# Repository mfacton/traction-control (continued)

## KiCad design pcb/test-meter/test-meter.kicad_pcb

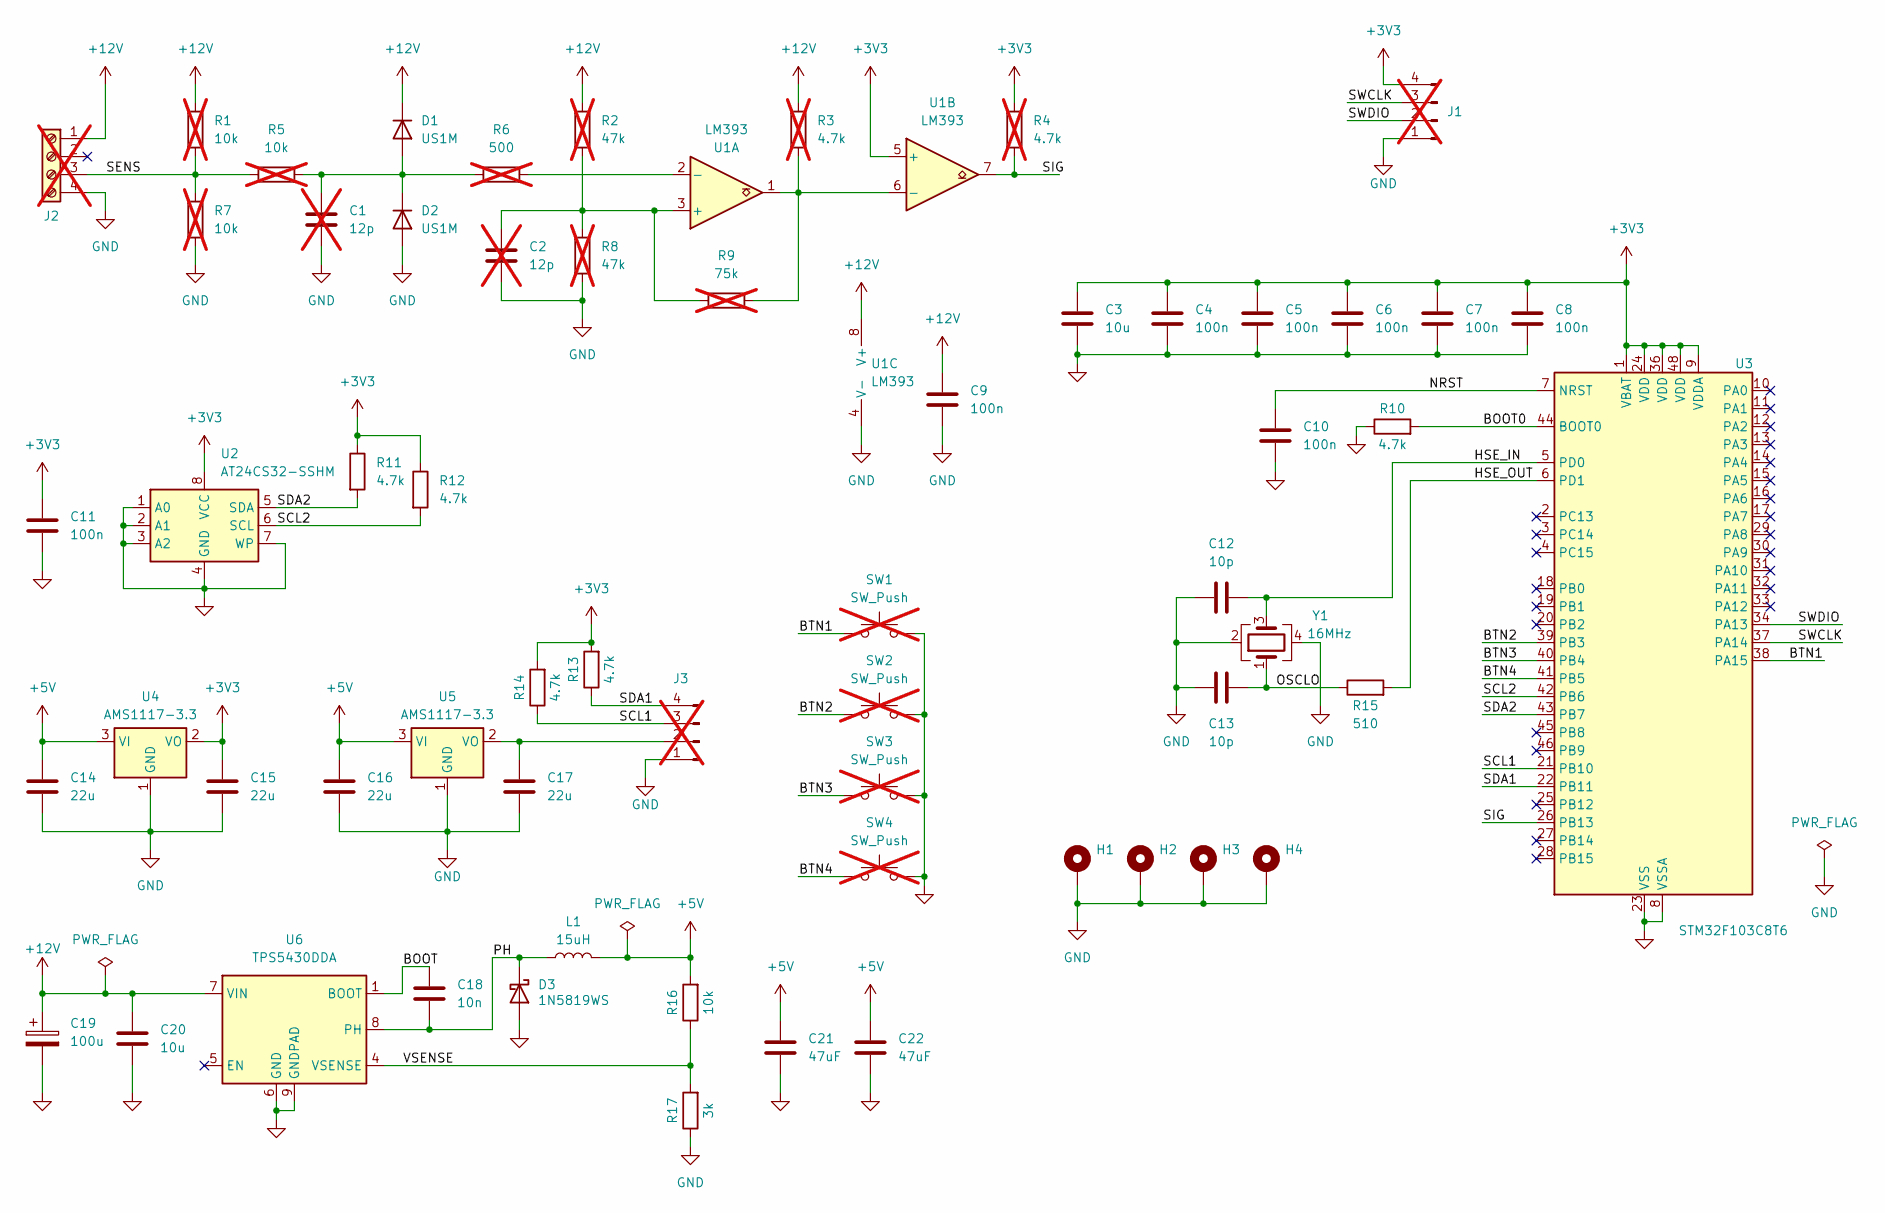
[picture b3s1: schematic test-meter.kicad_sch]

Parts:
C1, C2: 12p; C_Disc_D5.0mm_W2.5mm_P5.00mm; not fitted
C3: 10u; C_0603_1608Metric
C4, C5, C6, C7, C8, C9, C10, C11: 100n; C_0402_1005Metric
C12, C13: 10p; C_0402_1005Metric
C14, C15, C16, C17: 22u; C_0805_2012Metric
C18: 10n; C_0603_1608Metric
C19: 100u; C_Elec_8x6.2; LCSC C178539
C20: 10u; C_0805_2012Metric
C21, C22: 47uF; C_1206_3216Metric; LCSC C96123
D1, D2: US1M; D_SMA
D3: 1N5819WS; D_SOD-323
H1, H2, H3, H4: MountingHole_Pad; MountingHole_3.2mm_M3_DIN965_Pad
J1, J3: Conn_01x04_Pin; PinHeader_1x04_P2.54mm_Vertical; not fitted
J2: Screw_Terminal_01x04; TerminalBlock_bornier-4_P5.08mm; not fitted
L1: 15uH; L_Changjiang_FNR3010S; LCSC C222856
R1, R5, R7: 10k; R_Axial_DIN0207_L6.3mm_D2.5mm_P10.16mm_Horizontal; LCSC C17902; not fitted
R2, R8: 47k; R_Axial_DIN0207_L6.3mm_D2.5mm_P10.16mm_Horizontal; LCSC C25792; not fitted
R3, R4: 4.7k; R_Axial_DIN0207_L6.3mm_D2.5mm_P10.16mm_Horizontal; not fitted
R6: 500; R_Axial_DIN0207_L6.3mm_D2.5mm_P10.16mm_Horizontal; LCSC C17902; not fitted
R9: 75k; R_Axial_DIN0207_L6.3mm_D2.5mm_P10.16mm_Horizontal; LCSC C25798; not fitted
R10, R11, R12: 4.7k; R_0402_1005Metric; LCSC C25900
R13, R14: 4.7k; R_0402_1005Metric
R15: 510; R_0402_1005Metric; LCSC C25123
R16: 10k; R_0402_1005Metric; LCSC C25744
R17: 3k; R_0603_1608Metric_Pad0.98x0.95mm_HandSolder
SW1, SW2, SW3, SW4: SW_Push; SW_PUSH_6mm; not fitted
U1: LM393; SOIC-8_3.9x4.9mm_P1.27mm; LCSC C7955
U2: AT24CS32-SSHM; SOIC-8_3.9x4.9mm_P1.27mm; LCSC C6482
U3: STM32F103C8T6; LQFP-48_7x7mm_P0.5mm; LCSC C8734
U4, U5: AMS1117-3.3; SOT-223-3_TabPin2
U6: TPS5430DDA; TI_SO-PowerPAD-8_ThermalVias; LCSC C9864
Y1: 16MHz; Crystal_SMD_3225-4Pin_3.2x2.5mm

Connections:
+3V3: C3.1, C4.1, C5.1, C6.1, C7.1, C8.1, C11.1, C15.1, J1.4, R4.1, R11.1, R12.1, R13.2, R14.2, U1.5 (+), U2.8 (VCC), U3.1 (VBAT), U3.9 (VDDA), U3.24 (VDD), U3.36 (VDD), U3.48 (VDD), U4.2 (VO)
+5V: C14.1, C16.1, C21.1, C22.1, L1.2, R16.2, U4.3 (VI), U5.3 (VI)
+12V: C9.1, C19.1, C20.1, D1.1 (K), J2.1, R1.1, R2.1, R3.1, U1.8 (V+), U6.7 (VIN)
/BOOT: C18.1, U6.1 (BOOT)
/BOOT0: R10.2, U3.44 (BOOT0)
/BTN1: SW1.1, U3.38 (PA15)
/BTN2: SW2.1, U3.39 (PB3)
/BTN3: SW3.1, U3.40 (PB4)
/BTN4: SW4.1, U3.41 (PB5)
/HSE_IN: C12.2, U3.5 (PD0), Y1.3
/HSE_OUT: R15.2, U3.6 (PD1)
/NRST: C10.1, U3.7 (NRST)
/OSCLO: C13.2, R15.1, Y1.1
/PH: C18.2, D3.1 (K), L1.1, U6.8 (PH)
/SCL1: J3.3, R14.1, U3.21 (PB10)
/SCL2: R12.2, U2.6 (SCL), U3.42 (PB6)
/SDA1: J3.4, R13.1, U3.22 (PB11)
/SDA2: R11.2, U2.5 (SDA), U3.43 (PB7)
/SENS: J2.3, R1.2, R5.1, R7.1
/SIG: R4.2, U1.7, U3.26 (PB13)
/SWCLK: J1.3, U3.37 (PA14)
/SWDIO: J1.2, U3.34 (PA13)
/VSENSE: R16.1, R17.2, U6.4 (VSENSE)
GND: C1.2, C2.2, C3.2, C4.2, C5.2, C6.2, C7.2, C8.2, C9.2, C10.2, C11.2, C12.1, C13.1, C14.2, C15.2, C16.2, C17.2, C19.2, C20.2, C21.2, C22.2, D2.2 (A), D3.2 (A), H1.1, H2.1, H3.1, H4.1, J1.1, J2.4, J3.1, R7.2, R8.2, R10.1, R17.1, SW1.2, SW2.2, SW3.2, SW4.2, U1.4 (V-), U2.1 (A0), U2.2 (A1), U2.3 (A2), U2.4 (GND), U2.7 (WP), U3.8 (VSSA), U3.23 (VSS), U3.35 (VSS), U3.47 (VSS), U4.1 (GND), U5.1 (GND), U6.6 (GND), U6.9 (GNDPAD), Y1.2, Y1.4
unnamed: C1.1, D1.2 (A), D2.1 (K), R5.2, R6.1
unnamed: C17.1, J3.2, U5.2 (VO)
unnamed: C2.1, R2.2, R8.1, R9.1, U1.3 (+)
unnamed: R6.2, U1.2 (-)
unnamed: R3.2, R9.2, U1.1, U1.6 (-)

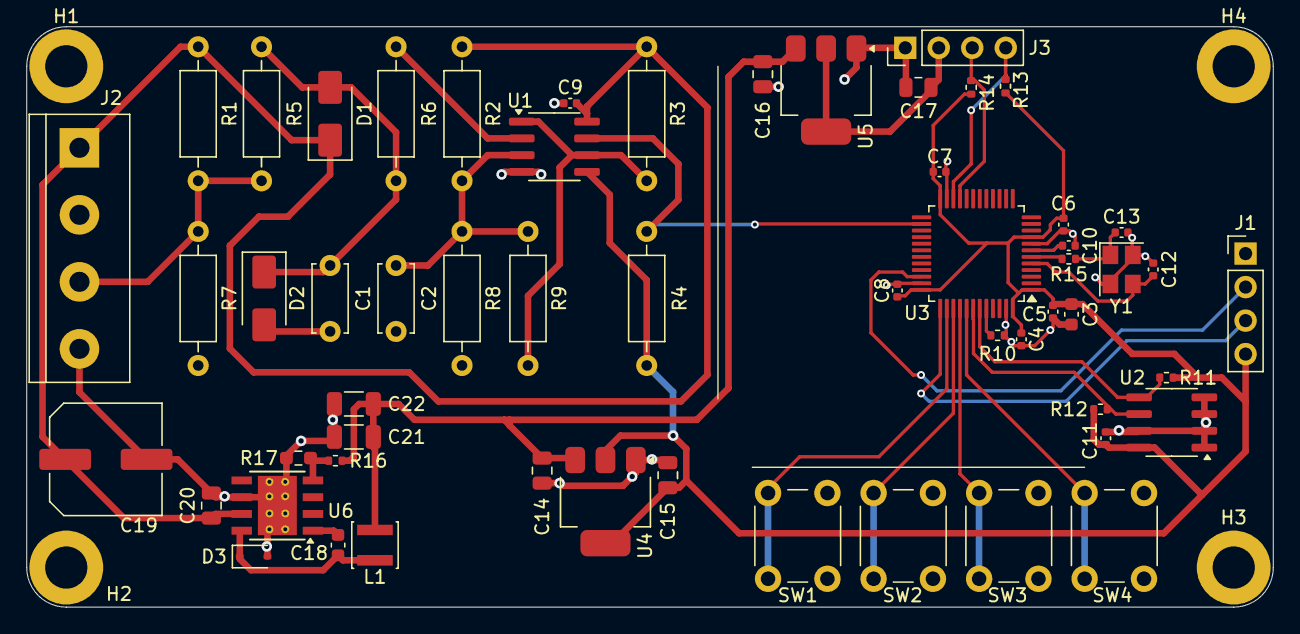
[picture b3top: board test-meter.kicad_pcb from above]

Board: 2 copper layers, 94.5 x 44.0 mm, 61 parts (0 on the bottom side), 29 nets.

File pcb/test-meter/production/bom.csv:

Designator,Footprint,Quantity,Value,LCSC Part #
"C10, C11, C4, C5, C6, C7, C8, C9",0402,8,100n,
"C12, C13",0402,2,10p,
"C14, C15, C16, C17",0805,4,22u,
C18,0603,1,10n,
C19,C_Elec_8x6.2,1,100u,C178539
C20,0805,1,10u,
"C21, C22",1206,2,47uF,C96123
C3,0603,1,10u,
"D1, D2",D_SMA,2,US1M,
D3,D_SOD-323,1,1N5819WS,
L1,L_Changjiang_FNR3010S,1,15uH,C222856
"R10, R11, R12",0402,3,4.7k,C25900
"R13, R14",0402,2,4.7k,
R15,0402,1,510,C25123
R16,0402,1,10k,C25744
R17,0603,1,3k,
U1,SOIC-8_3.9x4.9mm_P1.27mm,1,LM393,C7955
U2,SOIC-8_3.9x4.9mm_P1.27mm,1,AT24CS32-SSHM,C6482
U3,LQFP-48_7x7mm_P0.5mm,1,STM32F103C8T6,C8734
"U4, U5",SOT-223-3_TabPin2,2,AMS1117-3.3,
U6,TI_SO-PowerPAD-8_ThermalVias,1,TPS5430DDA,C9864
Y1,Crystal_SMD_3225-4Pin_3.2x2.5mm,1,16MHz,

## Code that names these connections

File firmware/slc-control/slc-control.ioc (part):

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Mcu.Name=STM32G431C(6-8-B)Tx
Mcu.Package=LQFP48
Mcu.UserName=STM32G431CBTx
PA0.GPIOParameters=GPIO_Label
PA0.GPIO_Label=SIG3
PA0.Mode=INP
PA0.Signal=COMP3_INP
PA1.GPIOParameters=GPIO_Label
PA1.GPIO_Label=SIG2
PA1.Mode=INP
PA1.Signal=COMP1_INP
PA10.GPIOParameters=GPIO_Label
PA10.GPIO_Label=DRDYM
PA10.Signal=GPXTI10
PA11.Mode=Device
PA11.Signal=USB_DM
PA12.Mode=Device
PA12.Signal=USB_DP
PA13.Mode=Trace_Asynchronous_SW
PA13.Signal=SYS_JTMS-SWDIO
PA14.Mode=Trace_Asynchronous_SW
PA14.Signal=SYS_JTCK-SWCLK
PA15.GPIOParameters=GPIO_Label
PA15.GPIO_Label=SCLE
PA15.Mode=I2C
PA15.Signal=I2C1_SCL
PA2.GPIOParameters=GPIO_Speed,PinState,GPIO_Label
PA2.GPIO_Label=CSP
PA2.GPIO_Speed=GPIO_SPEED_FREQ_HIGH
PA2.PinState=GPIO_PIN_SET
PA2.Signal=GPIO_Output
PA3.GPIOParameters=GPIO_Label
PA3.GPIO_Label=SIG1
PA3.Mode=INP
PA3.Signal=COMP2_INP
PA4.GPIOParameters=GPIO_Speed,PinState,GPIO_Label
PA4.GPIO_Label=CSG
PA4.GPIO_Speed=GPIO_SPEED_FREQ_HIGH
PA4.PinState=GPIO_PIN_SET
PA4.Signal=GPIO_Output
PA5.GPIOParameters=GPIO_Label
PA5.GPIO_Label=SCKM
PA5.Mode=Full_Duplex_Master
PA5.Signal=SPI1_SCK
PA6.GPIOParameters=GPIO_Label
PA6.GPIO_Label=MISOM
PA6.Mode=Full_Duplex_Master
PA6.Signal=SPI1_MISO
PA7.GPIOParameters=GPIO_Label
PA7.GPIO_Label=MOSIM
PA7.Mode=Full_Duplex_Master
PA7.Signal=SPI1_MOSI
PA8.GPIOParameters=GPIO_Label
PA8.GPIO_Label=SDAM
PA8.Mode=I2C
PA8.Signal=I2C2_SDA
PA9.GPIOParameters=GPIO_Label
PA9.GPIO_Label=SCLM
PA9.Mode=I2C
PA9.Signal=I2C2_SCL
PB0.GPIOParameters=GPIO_Label
PB0.GPIO_Label=INTG
PB0.Signal=GPXTI0
PB1.GPIOParameters=GPIO_Label
PB1.GPIO_Label=PPS
PB1.Signal=GPXTI1
PB10.GPIOParameters=GPIO_Label
PB10.GPIO_Label=GTX
PB10.Mode=Asynchronous
PB10.Signal=USART3_TX
PB11.GPIOParameters=GPIO_Label
PB11.GPIO_Label=GRX
PB11.Mode=Asynchronous
PB11.Signal=USART3_RX
PB12.GPIOParameters=GPIO_Speed,GPIO_Label
PB12.GPIO_Label=DC
PB12.GPIO_Speed=GPIO_SPEED_FREQ_HIGH
PB12.Signal=GPIO_Output
PB13.GPIOParameters=GPIO_Speed,GPIO_Label
PB13.GPIO_Label=SCKD
PB13.GPIO_Speed=GPIO_SPEED_FREQ_HIGH
PB13.Mode=TX_Only_Simplex_Unidirect_Master
PB13.Signal=SPI2_SCK
PB14.GPIOParameters=GPIO_Speed,GPIO_Label
PB14.GPIO_Label=CSD
PB14.GPIO_Speed=GPIO_SPEED_FREQ_HIGH
PB14.Signal=GPIO_Output
PB15.GPIOParameters=GPIO_Speed,GPIO_Label
PB15.GPIO_Label=MOSID
PB15.GPIO_Speed=GPIO_SPEED_FREQ_HIGH
PB15.Mode=TX_Only_Simplex_Unidirect_Master
PB15.Signal=SPI2_MOSI
PB2.GPIOParameters=GPIO_Label
PB2.GPIO_Label=DRDYP
PB2.Signal=GPXTI2
PB3.Mode=Trace_Asynchronous_SW
PB3.Signal=SYS_JTDO-SWO
PB4.GPIOParameters=GPIO_Speed,GPIO_Label
PB4.GPIO_Label=DRV1
PB4.GPIO_Speed=GPIO_SPEED_FREQ_MEDIUM
PB4.Signal=GPIO_Output
PB5.GPIOParameters=GPIO_Speed,GPIO_Label
PB5.GPIO_Label=DRV2
PB5.GPIO_Speed=GPIO_SPEED_FREQ_MEDIUM
PB5.Signal=GPIO_Output
PB6.GPIOParameters=GPIO_Label
PB6.GPIO_Label=REPH
PB6.Signal=S_TIM8_CH1
PB7.GPIOParameters=GPIO_Label
PB7.GPIO_Label=SDAE
PB7.Mode=I2C
PB7.Signal=I2C1_SDA
PB8-BOOT0.GPIOParameters=GPIO_PuPd,GPIO_Label
PB8-BOOT0.GPIO_Label=BTN4
PB8-BOOT0.GPIO_PuPd=GPIO_PULLUP
PB8-BOOT0.Signal=GPIO_Input
PB9.GPIOParameters=GPIO_Label
PB9.GPIO_Label=REPL
PB9.Signal=S_TIM8_CH3
PC13.GPIOParameters=GPIO_PuPd,GPIO_Label
PC13.GPIO_Label=BTN3
PC13.GPIO_PuPd=GPIO_PULLUP
PC13.Signal=GPIO_Input
PC14-OSC32_IN.GPIOParameters=GPIO_PuPd,GPIO_Label
PC14-OSC32_IN.GPIO_Label=BTN2
PC14-OSC32_IN.GPIO_PuPd=GPIO_PULLUP
PC14-OSC32_IN.Signal=GPIO_Input
PC15-OSC32_OUT.GPIOParameters=GPIO_PuPd,GPIO_Label
PC15-OSC32_OUT.GPIO_Label=BTN1
PC15-OSC32_OUT.GPIO_PuPd=GPIO_PULLUP
PC15-OSC32_OUT.Signal=GPIO_Input
PF0-OSC_IN.Mode=HSE-External-Oscillator
PF0-OSC_IN.Signal=RCC_OSC_IN
PF1-OSC_OUT.Mode=HSE-External-Oscillator
PF1-OSC_OUT.Signal=RCC_OSC_OUT
RCC.HSE_VALUE=16000000
RCC.SYSCLKFreq_VALUE=144000000
RCC.SYSCLKSource=RCC_SYSCLKSOURCE_PLLCLK
board=custom

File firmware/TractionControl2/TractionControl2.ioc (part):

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Mcu.Name=STM32G431C(6-8-B)Tx
Mcu.Package=LQFP48
Mcu.UserName=STM32G431CBTx
PA0.GPIOParameters=GPIO_Label
PA0.GPIO_Label=TACH
PA0.Mode=INP
PA0.Signal=COMP3_INP
PA1.GPIOParameters=GPIO_Label
PA1.GPIO_Label=SIG2
PA1.Mode=INP
PA1.Signal=COMP1_INP
PA11.GPIOParameters=GPIO_Speed,GPIO_Label
PA11.GPIO_Label=PGPS
PA11.GPIO_Speed=GPIO_SPEED_FREQ_LOW
PA11.Signal=GPIO_Output
PA13.Mode=Trace_Asynchronous_SW
PA13.Signal=SYS_JTMS-SWDIO
PA14.Mode=Trace_Asynchronous_SW
PA14.Signal=SYS_JTCK-SWCLK
PA15.GPIOParameters=GPIO_Label
PA15.GPIO_Label=SCLE
PA15.Mode=I2C
PA15.Signal=I2C1_SCL
PA3.GPIOParameters=GPIO_Label
PA3.GPIO_Label=SIG1
PA3.Mode=INP
PA3.Signal=COMP2_INP
PA5.GPIOParameters=GPIO_PuPd,GPIO_Label
PA5.GPIO_Label=BTN3
PA5.GPIO_PuPd=GPIO_PULLUP
PA5.Signal=GPIO_Input
PA8.GPIOParameters=GPIO_Label
PA8.GPIO_Label=SDAD
PA8.Mode=I2C
PA8.Signal=I2C2_SDA
PA9.GPIOParameters=GPIO_Label
PA9.GPIO_Label=SCLD
PA9.Mode=I2C
PA9.Signal=I2C2_SCL
PB0.GPIOParameters=GPIO_Label
PB0.GPIO_Label=TACH
PB0.Mode=INP
PB0.Signal=COMP4_INP
PB11.GPIOParameters=GPIO_Speed,GPIO_Label
PB11.GPIO_Label=DRV2
PB11.GPIO_Speed=GPIO_SPEED_FREQ_MEDIUM
PB11.Signal=GPIO_Output
PB12.GPIOParameters=GPIO_Speed,GPIO_Label
PB12.GPIO_Label=DRV1
PB12.GPIO_Speed=GPIO_SPEED_FREQ_MEDIUM
PB12.Signal=GPIO_Output
PB2.GPIOParameters=GPIO_PuPd,GPIO_Label
PB2.GPIO_Label=BTN4
PB2.GPIO_PuPd=GPIO_PULLUP
PB2.Signal=GPIO_Input
PB3.Mode=Trace_Asynchronous_SW
PB3.Signal=SYS_JTDO-SWO
PB5.GPIOParameters=GPIO_PuPd,GPIO_Label
PB5.GPIO_Label=BTN2
PB5.GPIO_PuPd=GPIO_PULLUP
PB5.Signal=GPIO_Input
PB6.GPIOParameters=GPIO_Speed,GPIO_Label
PB6.GPIO_Label=GPS_TX
PB6.GPIO_Speed=GPIO_SPEED_FREQ_HIGH
PB6.Mode=Asynchronous
PB6.Signal=USART1_TX
PB7.GPIOParameters=GPIO_Speed,GPIO_Label
PB7.GPIO_Label=GPS_RX
PB7.GPIO_Speed=GPIO_SPEED_FREQ_HIGH
PB7.Mode=Asynchronous
PB7.Signal=USART1_RX
PB9.GPIOParameters=GPIO_Label
PB9.GPIO_Label=SDAE
PB9.Mode=I2C
PB9.Signal=I2C1_SDA
PC13.GPIOParameters=GPIO_PuPd,GPIO_Label
PC13.GPIO_Label=BTN1
PC13.GPIO_PuPd=GPIO_PULLUP
PC13.Signal=GPIO_Input
PF0-OSC_IN.Mode=HSE-External-Oscillator
PF0-OSC_IN.Signal=RCC_OSC_IN
PF1-OSC_OUT.Mode=HSE-External-Oscillator
PF1-OSC_OUT.Signal=RCC_OSC_OUT
RCC.HSE_Timout=100
RCC.HSE_VALUE=16000000
RCC.SYSCLKFreq_VALUE=170000000
RCC.SYSCLKSource=RCC_SYSCLKSOURCE_PLLCLK
board=custom

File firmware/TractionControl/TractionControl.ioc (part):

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Mcu.Name=STM32F103C(8-B)Tx
Mcu.Package=LQFP48
Mcu.UserName=STM32F103C8Tx
PA10.Mode=Asynchronous
PA10.Signal=USART1_RX
PA13.Mode=Trace_Asynchronous_SW
PA13.Signal=SYS_JTMS-SWDIO
PA14.Mode=Trace_Asynchronous_SW
PA14.Signal=SYS_JTCK-SWCLK
PA3.GPIOParameters=GPIO_Label
PA3.GPIO_Label=SIG2
PA3.Signal=GPXTI3
PA4.GPIOParameters=GPIO_Label
PA4.GPIO_Label=SIG1
PA4.Signal=GPXTI4
PA5.Signal=ADCx_IN5
PA6.GPIOParameters=GPIO_Label
PA6.GPIO_Label=DRV2
PA6.Signal=GPIO_Output
PA7.GPIOParameters=GPIO_Label
PA7.GPIO_Label=DRV1
PA7.Signal=GPIO_Output
PA9.Mode=Asynchronous
PA9.Signal=USART1_TX
PB10.Mode=I2C
PB10.Signal=I2C2_SCL
PB11.Mode=I2C
PB11.Signal=I2C2_SDA
PB12.GPIOParameters=GPIO_Label
PB12.GPIO_Label=PGPS
PB12.Signal=GPIO_Output
PB3.Mode=Trace_Asynchronous_SW
PB3.Signal=SYS_JTDO-TRACESWO
PB6.Mode=I2C
PB6.Signal=I2C1_SCL
PB7.Mode=I2C
PB7.Signal=I2C1_SDA
PB8.GPIOParameters=GPIO_PuPd,GPIO_Label
PB8.GPIO_Label=BTN1
PB8.GPIO_PuPd=GPIO_PULLUP
PB8.Signal=GPIO_Input
PB9.GPIOParameters=GPIO_PuPd,GPIO_Label
PB9.GPIO_Label=BTN2
PB9.GPIO_PuPd=GPIO_PULLUP
PB9.Signal=GPIO_Input
PC14-OSC32_IN.GPIOParameters=GPIO_PuPd,GPIO_Label
PC14-OSC32_IN.GPIO_Label=BTN3
PC14-OSC32_IN.GPIO_PuPd=GPIO_PULLUP
PC14-OSC32_IN.Signal=GPIO_Input
PC15-OSC32_OUT.GPIOParameters=GPIO_PuPd,GPIO_Label
PC15-OSC32_OUT.GPIO_Label=BTN4
PC15-OSC32_OUT.GPIO_PuPd=GPIO_PULLUP
PC15-OSC32_OUT.Signal=GPIO_Input
PD0-OSC_IN.Mode=HSE-External-Oscillator
PD0-OSC_IN.Signal=RCC_OSC_IN
PD1-OSC_OUT.Mode=HSE-External-Oscillator
PD1-OSC_OUT.Signal=RCC_OSC_OUT
RCC.HSEDivPLL=RCC_HSE_PREDIV_DIV2
RCC.HSE_VALUE=16000000
RCC.SYSCLKFreq_VALUE=72000000
RCC.SYSCLKSource=RCC_SYSCLKSOURCE_PLLCLK
board=custom

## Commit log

2024-05-10 Add gitignore
2024-06-06 Update gitignore
2024-06-06 Add test-meter pcb
2024-06-06 Ignore stm32 debug
2024-06-06 Add test-meter stm32 code
2024-06-06 Remove OS ignore garbage
2024-06-06 Remove python ignore
2024-06-07 Add old documents
2024-06-10 Setup stm32 project
2024-06-10 Finish placing and route power
2024-06-13 Save
2024-06-13 Revision and production files
2024-06-13 Configure pins
2024-06-23 Add labeling silkmask
2024-07-01 Finish base program
2024-07-01 Finish schematic except pins
2024-07-05 Final pcb
2024-07-05 Create bulk program
2024-07-05 Ignore usb device
2024-07-06 Ignore release
2024-07-06 Add release configuration
2024-07-06 Make production files
2024-07-06 Finish testing with gps
2024-07-06 Configure rev2 pinout
2024-07-06 Basic configuration of ioc
2024-07-07 Finish layout
2024-07-07 Configure peripheral pins
2024-07-07 Change extended parts to do not place
2024-07-07 Final production
2024-07-14 Fix power connection
2024-07-14 Program traction control rev2
2024-07-14 Add menu system changes
2024-07-14 Fix auxilary output
2024-07-15 Add some notes about gps
2024-07-17 Reinit project
2024-07-23 Re-export for manucaturing
2024-07-23 Change user and drill origins
2024-07-26 Add gps precompile
2024-07-26 Fix ssd1309 reset input voltage
2024-07-26 Setup traction control firmware
2024-09-04 Save old slc control firmware
2024-09-04 Implement all stm-lib libraries
2024-09-04 Apply small changes to menu
2024-10-21 Add photo
2025-01-04 Move slc-control to seperate repo
